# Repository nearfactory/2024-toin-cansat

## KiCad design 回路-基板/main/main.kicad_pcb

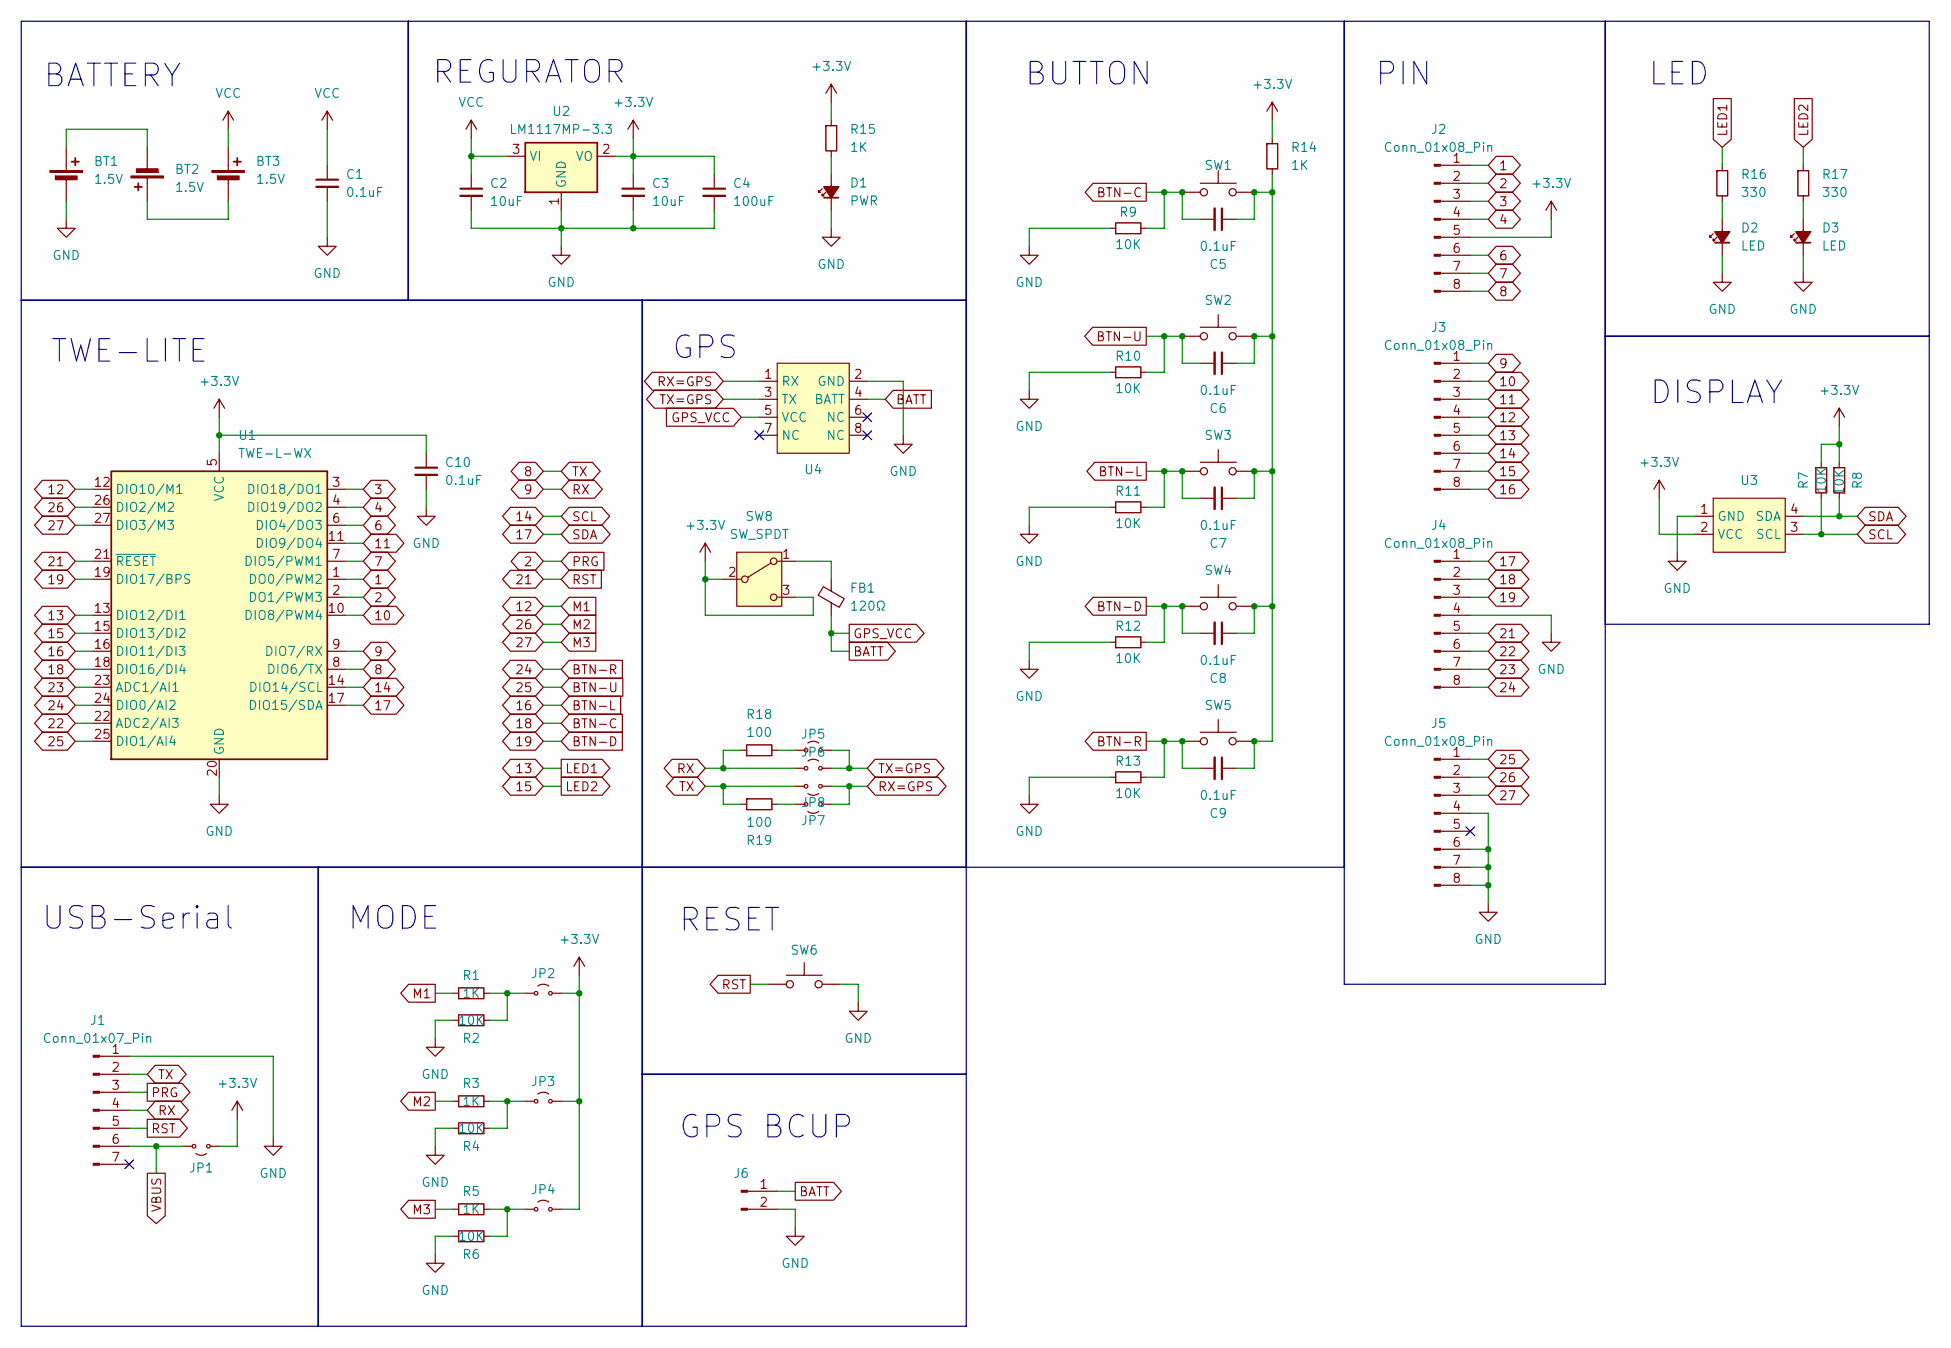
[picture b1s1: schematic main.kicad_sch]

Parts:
BT1, BT2, BT3: 1.5V; AAA-holder
C1, C5, C6, C7, C8, C9, C10: 0.1uF; C_0805_2012Metric
C2, C3: 10uF; C_0805_2012Metric
C4: 100uF; CP_Radial_D6.3mm_P2.50mm
D1: PWR; LED_0805_2012Metric
D2, D3: LED; LED_0805_2012Metric
FB1: 120Ω; L_0603_1608Metric
J1: Conn_01x07_Pin; PinSocket_1x07_P2.54mm_Vertical
J2, J3, J4, J5: Conn_01x08_Pin; Pin-Extender
J6: Conn_01x02_Pin; PinSocket_1x02_P2.54mm_Vertical
JP1, JP2, JP3, JP4, JP5, JP6, JP7, JP8: Jumper_2_Small_Open; SolderJumper-2_P1.3mm_Open_RoundedPad1.0x1.5mm
R1, R3, R5, R14, R15: 1K; R_0805_2012Metric
R2, R4, R6, R7, R8, R9, R10, R11, R12, R13: 10K; R_0805_2012Metric
R16, R17: 330; R_0805_2012Metric
R18, R19: 100; R_0805_2012Metric
SW1, SW2, SW3, SW4, SW5: SW_Push; TVBP06-B043C
SW6: SW_Push; Tactile1
SW8: SW_SPDT; SS12D01G4
U1: TWE-L-WX; MonoWireless_TWE-L-WX
U2: LM1117MP-3.3; SOT-223-3_TabPin2
U3: Display
U4: GPS-54D-014

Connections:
1: J2.1, U1.1 (DO0/PWM2)
2: J1.3, J2.2, U1.2 (DO1/PWM3)
3: J2.3, U1.3 (DIO18/DO1)
4: J2.4, U1.4 (DIO19/DO2)
6: J2.6, U1.6 (DIO4/DO3)
7: J2.7, U1.7 (DIO5/PWM1)
8: J1.2, J2.8, JP8.1 (A), R19.1, U1.8 (DIO6/TX)
9: J1.4, J3.1, JP6.1 (A), R18.1, U1.9 (DIO7/RX)
10: J3.2, U1.10 (DIO8/PWM4)
11: J3.3, U1.11 (DIO9/DO4)
12: J3.4, R1.1, U1.12 (DIO10/M1)
13: J3.5, R16.1, U1.13 (DIO12/DI1)
14: J3.6, R7.2, U1.14 (DIO14/SCL), U3.3 (SCL)
15: J3.7, R17.1, U1.15 (DIO13/DI2)
16: C7.2, J3.8, R11.2, SW3.1, U1.16 (DIO11/DI3)
17: J4.1, R8.2, U1.17 (DIO15/SDA), U3.4 (SDA)
18: C5.2, J4.2, R9.2, SW1.1, U1.18 (DIO16/DI4)
19: C8.2, J4.3, R12.2, SW4.1, U1.19 (DIO17/BPS)
21: J1.5, J4.5, SW6.1, U1.21 (~RESET); also elsewhere on the board
22: J4.6, U1.22 (ADC2/AI3)
23: J4.7, U1.23 (ADC1/AI1)
24: C9.2, J4.8, R13.2, SW5.1, U1.24 (DIO0/AI2)
25: C6.2, J5.1, R10.2, SW2.1, U1.25 (DIO1/AI4)
26: J5.2, R3.1, U1.26 (DIO2/M2)
27: J5.3, R5.1, U1.27 (DIO3/M3)
+3.3V: C3.1, C4.1, C10.1, J2.5, JP1.1 (A), JP2.2 (B), JP3.2 (B), JP4.2 (B), R7.1, R8.1, R14.1, R15.1, SW8.2 (B), SW8.3 (C), U1.5 (VCC), U2.2 (VO), U3.2 (VCC); also elsewhere on the board
BATT: FB1.2, J6.1, U4.4 (BATT), U4.5 (VCC)
GND: BT1.2 (-), C1.2, C2.2, C3.2, C4.2, C10.2, D1.1 (K), D2.1 (K), D3.1 (K), J1.1, J4.4, J5.4, J5.6, J5.7, J5.8, J6.2, R2.1, R4.1, R6.1, R9.1, R10.1, R11.1, R12.1, R13.1, SW6.2, U1.20 (GND), U1.28 (GND), U1.30 (GND), U1.31 (GND), U1.32 (GND), U2.1 (GND), U3.1 (GND), U4.2 (GND); also elsewhere on the board
unnamed: BT1.1 (+), BT2.2 (-)
unnamed: BT2.1 (+), BT3.2 (-)
unnamed: C5.1, C6.1, C7.1, C8.1, C9.1, R14.2, SW1.2, SW2.2, SW3.2, SW4.2, SW5.2
unnamed 31: D1.2 (A), R15.2; also elsewhere on the board
unnamed: D2.2 (A), R16.2
unnamed: D3.2 (A), R17.2
unnamed 34: JP2.1 (A), R1.2, R2.2; also elsewhere on the board
unnamed 35: JP3.1 (A), R3.2, R4.2; also elsewhere on the board
unnamed 36: JP4.1 (A), R5.2, R6.2; also elsewhere on the board
unnamed: JP5.1 (A), R18.2
unnamed: JP7.1 (A), R19.2
unnamed: FB1.1, SW8.1 (A)
RX=GPS: JP7.2 (B), JP8.2 (B), U4.1 (RX)
TX=GPS: JP5.2 (B), JP6.2 (B), U4.3 (TX)
VBUS: J1.6, JP1.2 (B); also elsewhere on the board
VCC: BT3.1 (+), C1.1, C2.1, U2.3 (VI)

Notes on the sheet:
GPS BCUP
DISPLAY
REGURATOR
RESET
TWE-LITE
USB-Serial
BUTTON
BATTERY
LED
GPS
MODE
PIN

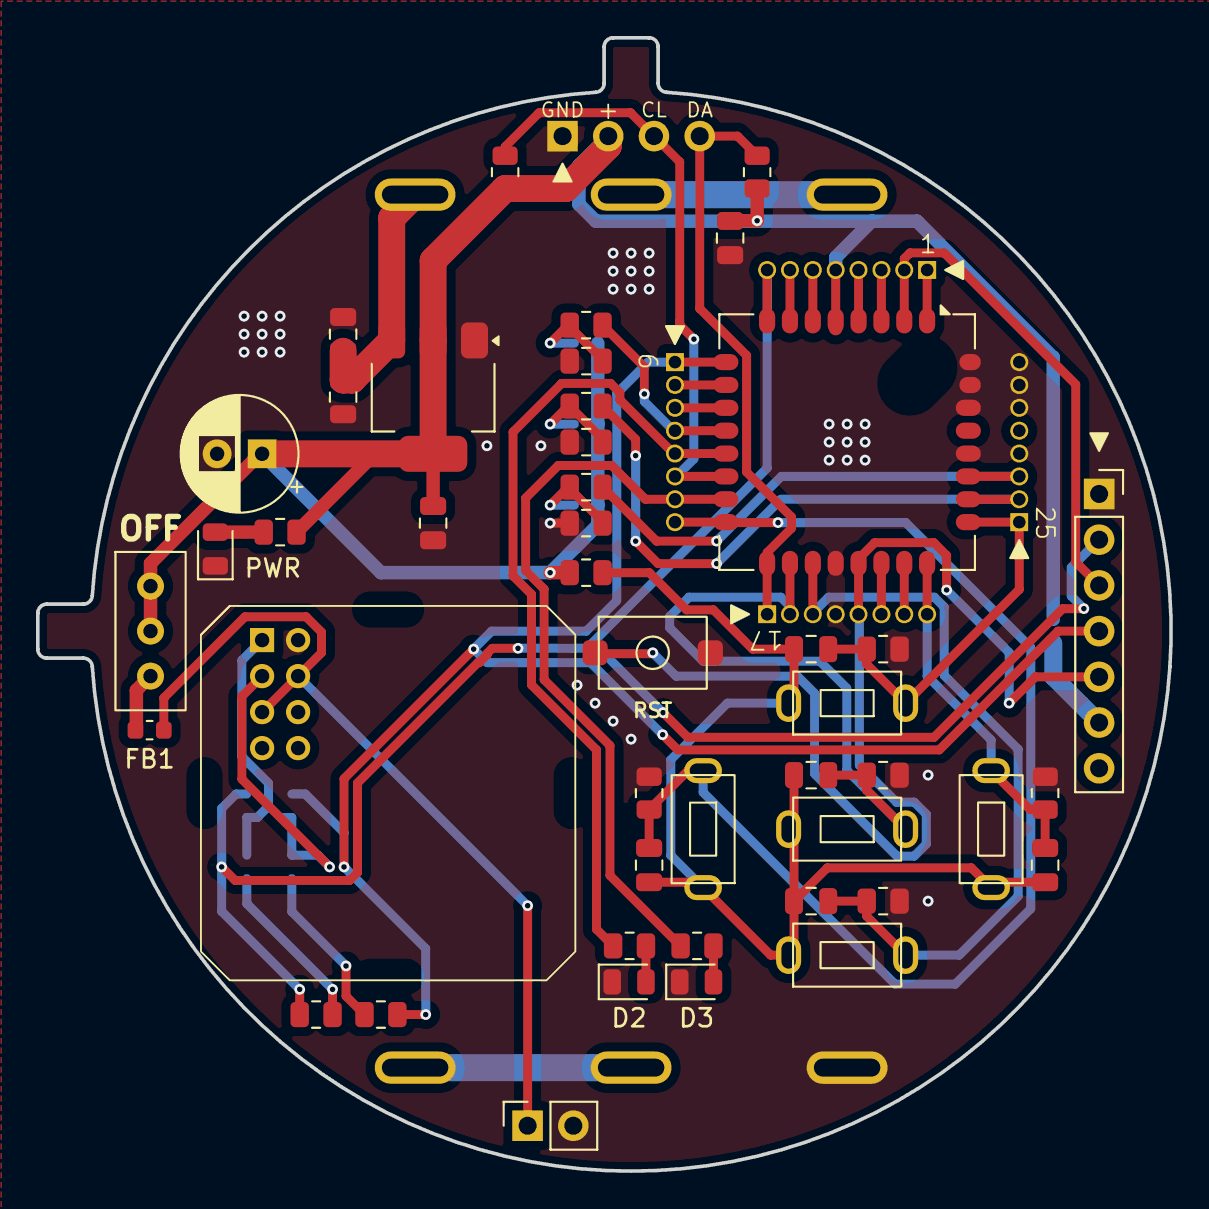
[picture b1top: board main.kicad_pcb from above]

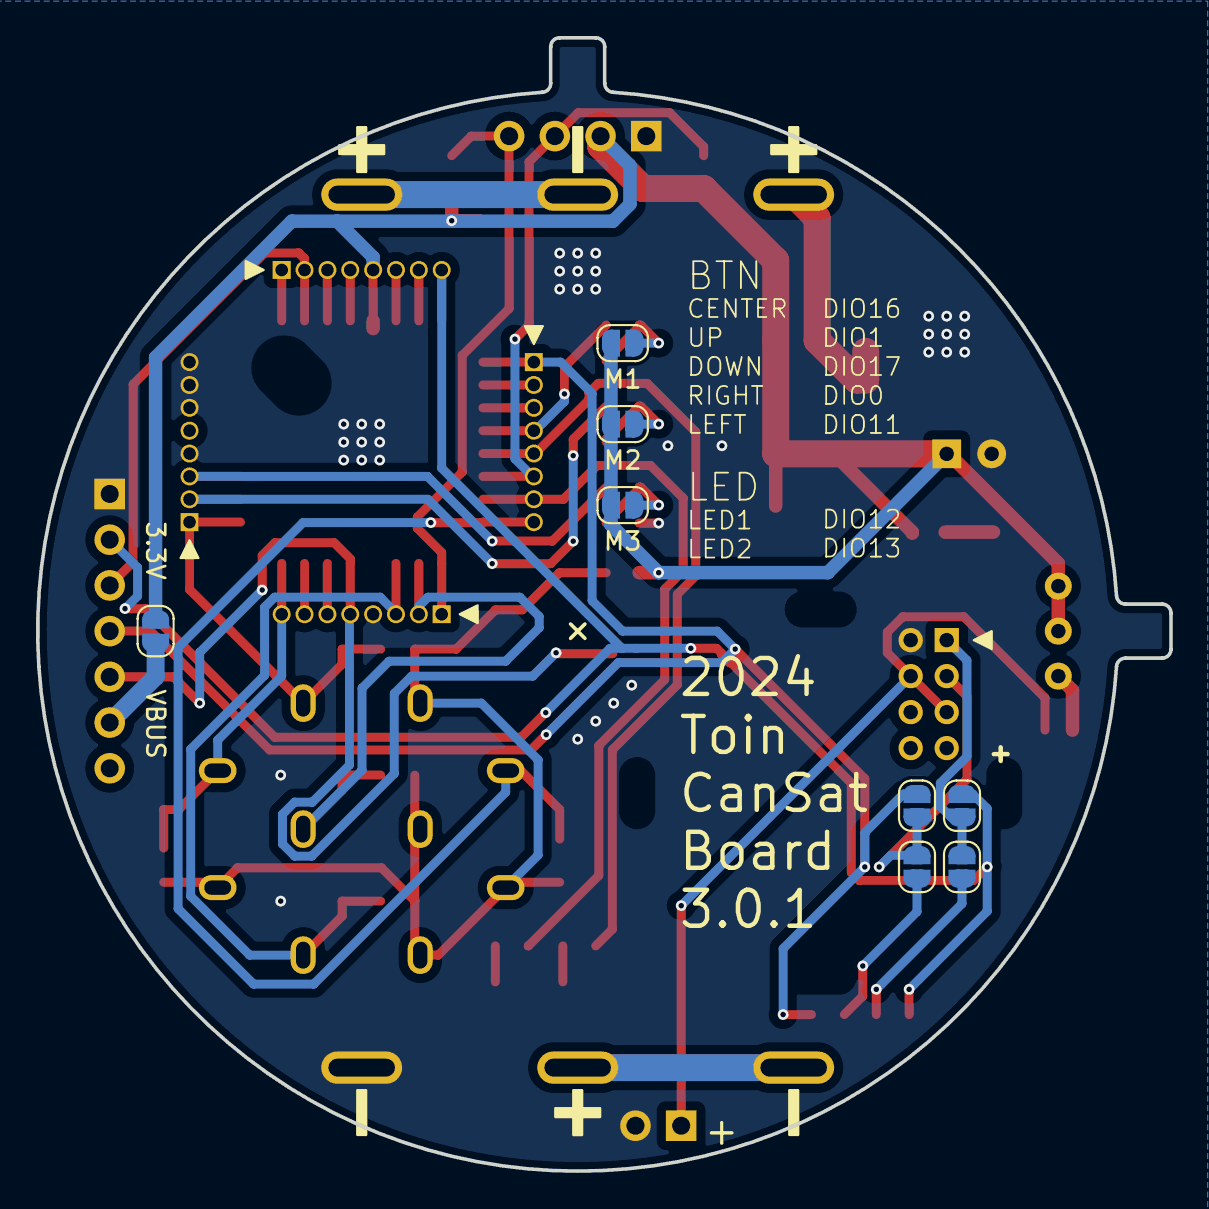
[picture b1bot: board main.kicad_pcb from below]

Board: 2 copper layers, 63.0 x 63.0 mm, 61 parts (11 on the bottom side), 44 nets.

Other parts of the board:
3.3V        VBUS: Jumper_2_Small_Open; SolderJumper-2_P1.3mm_Open_RoundedPad1.0x1.5mm
M1, M2, M3: Jumper_2_Small_Open; SolderJumper-2_P1.3mm_Open_RoundedPad1.0x1.5mm
PWR: PWR; LED_0805_2012Metric
RST: SW_Push; Tactile1

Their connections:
21: RST.1; also elsewhere on the board
+3.3V: 3.3V VBUS.1 (A), M1.2 (B), M2.2 (B), M3.2 (B); also elsewhere on the board
GND: PWR.1 (K), RST.2; also elsewhere on the board
unnamed 31: PWR.2 (A); also elsewhere on the board
unnamed 34: M1.1 (A); also elsewhere on the board
unnamed 35: M2.1 (A); also elsewhere on the board
unnamed 36: M3.1 (A); also elsewhere on the board
VBUS: 3.3V VBUS.2 (B); also elsewhere on the board

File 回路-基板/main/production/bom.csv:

Designator,Footprint,Quantity,Value,LCSC Part #
3.3V        VBUS,SolderJumper-2_P1.3mm_Open_RoundedPad1.0x1.5mm,1,Jumper_2_Small_Open,
"BT1, BT2, BT3",AAA-holder,3,1.5V,
"C1, C10, C5, C6, C7, C8, C9",0805,7,0.1uF,
"C2, C3",0805,2,10uF,
C4,CP_Radial_D6.3mm_P2.50mm,1,100uF,
"D2, D3",0805,2,LED,
FB1,0603,1,FerriteBead_Small,
J1,PinSocket_1x07_P2.54mm_Vertical,1,Conn_01x07_Pin,
"J2, J3, J4, J5",Pin-Extender,4,Conn_01x08_Pin,
"PRG, RST",Tactile1,2,SW_Push,
PWR,0805,1,PWR,
"R1, R14, R15, R3, R5",0805,5,1K,
"R10, R11, R12, R13, R2, R4, R6, R7, R8, R9",0805,10,10K,
"R16, R17",0805,2,330,
"SW1, SW2, SW3, SW4, SW5",TVBP06-B043C,5,SW_Push,
SW8,SS12D01G4,1,SW_SPDT,
U1,MonoWireless_TWE-L-WX,1,TWE-L-WX,
U2,SOT-223-3_TabPin2,1,LM1117MP-3.3,
U3,Display,1,~,
U4,GPS-54D-014,1,~,

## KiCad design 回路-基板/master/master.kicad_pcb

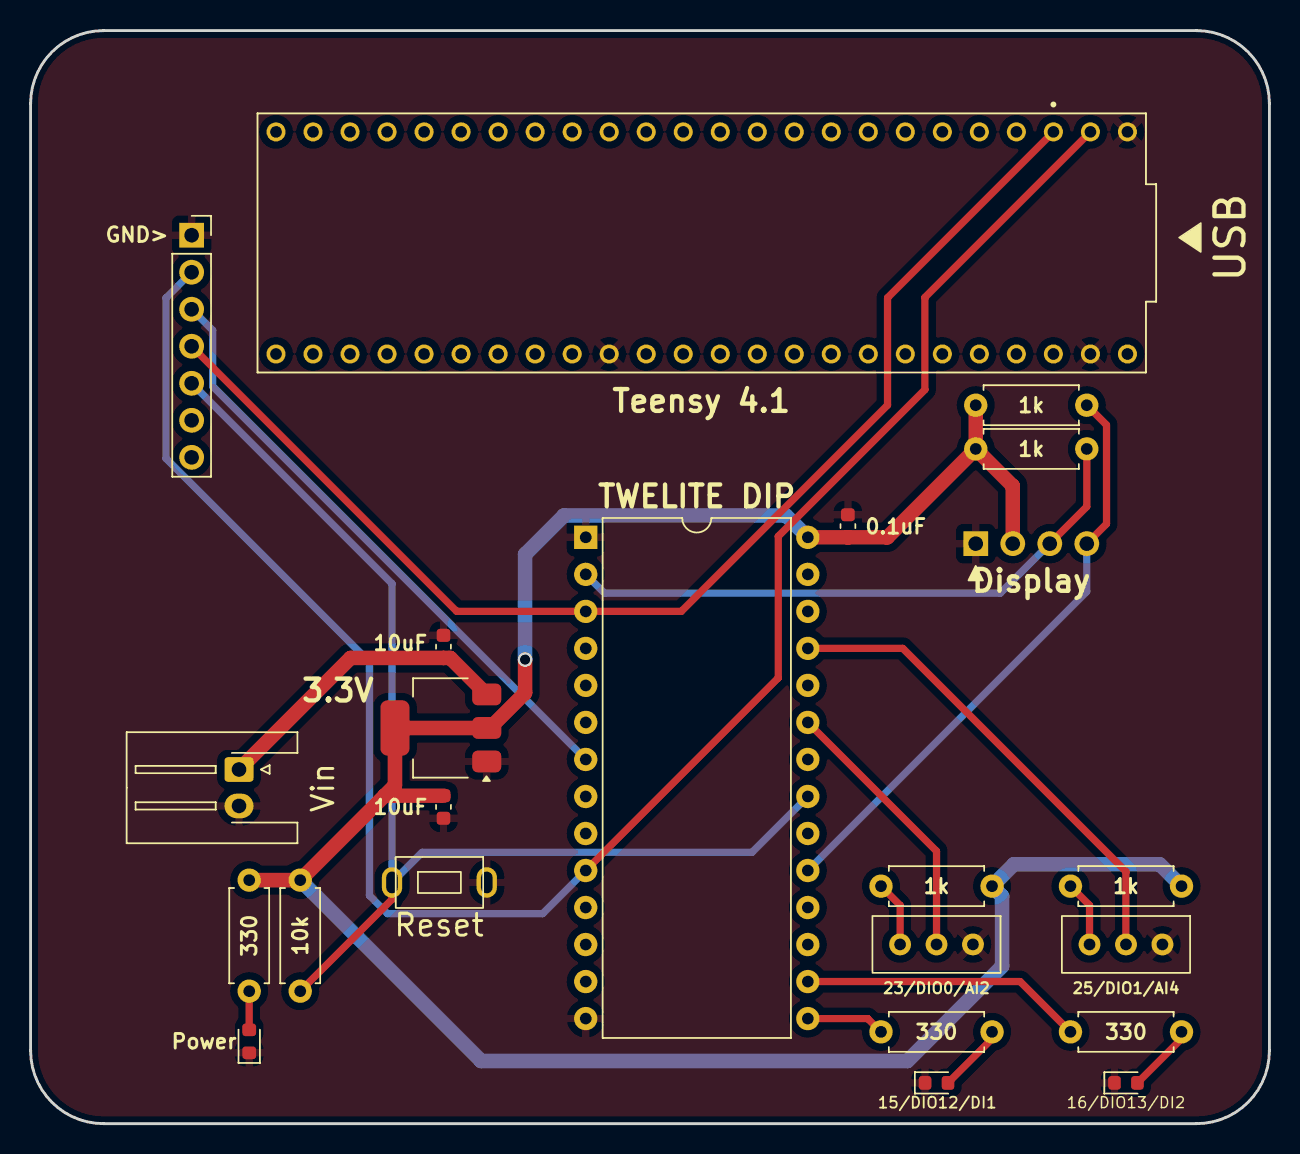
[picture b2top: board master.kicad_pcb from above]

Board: 2 copper layers, 85.0 x 75.0 mm, 23 parts (0 on the bottom side), 18 nets.

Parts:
3.3V: LM1117MP-3.3; SOT-223-3_TabPin2
15/DIO12/DI1: LED1; LED_0603_1608Metric
16/DIO13/DI2: LED2; LED_0603_1608Metric
23/DIO0/AI2, 25/DIO1/AI4: SW_SPDT; SS12D01G4
C1, C3: 10uF; C_0603_1608Metric
C2: 0.1uF; C_0603_1608Metric
Display: Display
GND>: Conn_01x07_Pin; PinSocket_1x07_P2.54mm_Vertical
Power: PWR; LED_0603_1608Metric
R1, R2, R3: 330; R_Axial_DIN0207_L6.3mm_D2.5mm_P7.62mm_Horizontal
R4, R5: 1K; R_Axial_DIN0207_L6.3mm_D2.5mm_P7.62mm_Horizontal
R6: 10K; R_Axial_DIN0207_L6.3mm_D2.5mm_P7.62mm_Horizontal
R7, R8: R_Small; R_Axial_DIN0207_L6.3mm_D2.5mm_P7.62mm_Horizontal
Reset: RESET; TVBP06-B043C
TWELITE DIP: TWE-L-DP-W; DIP-28_W15.24mm
Teensy 4.1: DEV-16771; MODULE_DEV-16771
Vin: Ext. PWR; JST_XH_S2B-XH-A-1_1x02_P2.50mm_Horizontal

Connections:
2: Display.3 (SCL), R4.1, TWELITE DIP.2 (DIO14/SCL)
3: GND>.4, TWELITE DIP.3 (DIO7/RX), Teensy 4.1.1 (TX1)
7: GND>.3, TWELITE DIP.7 (DO1/PWM3)
10: GND>.2, TWELITE DIP.10 (DIO6/TX), Teensy 4.1.0 (RX1)
15: R2.1, TWELITE DIP.15 (DIO12/DI1)
16: R3.1, TWELITE DIP.16 (DIO13/DI2)
19: Display.4 (SDA), R5.1, TWELITE DIP.19 (DIO15/SDA)
21: GND>.5, R6.2, Reset.1, TWELITE DIP.21 (~RESET)
23: 23/DIO0/AI2.2 (B), TWELITE DIP.23 (DIO0/AI2)
25: 25/DIO1/AI4.2 (B), TWELITE DIP.25 (DIO1/AI4)
+3.3V: 3.3V.2 (VO), C2.1, C3.1, Display.2 (VCC), R1.1, R4.2, R5.2, R6.1, R7.2, R8.2, TWELITE DIP.28 (VCC)
GND: 3.3V.1 (GND), 15/DIO12/DI1.1 (K), 16/DIO13/DI2.1 (K), 23/DIO0/AI2.3 (C), 25/DIO1/AI4.3 (C), C1.2, C2.2, C3.2, Display.1 (GND), GND>.1, Power.1 (K), Reset.2, TWELITE DIP.1 (GND), TWELITE DIP.14 (GND), Teensy 4.1.GND1 (GND), Teensy 4.1.GND2 (GND), Teensy 4.1.GND3 (GND), Vin.2
unnamed: Power.2 (A), R1.2
unnamed: 15/DIO12/DI1.2 (A), R2.2
unnamed: 16/DIO13/DI2.2 (A), R3.2
unnamed: 3.3V.3 (VI), C1.1, Vin.1
unnamed: 23/DIO0/AI2.1 (A), R7.1
unnamed: 25/DIO1/AI4.1 (A), R8.1

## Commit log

2024-04-11 TWE-LITEデータシートの追加
2024-04-11 回路関連のプッシュ
2024-04-11 TWE-LITE-RED_symbol
2024-04-11 過去作の追加
2024-04-16 3Dモデルをアップロード
    よろちく～～～～～
2024-04-16 3Dモデルの名前変更した
2024-04-17 回路をアップデートした
2024-04-19 回路やったぜぇ
2024-04-19 回路更新
2024-04-20 右下のトランジスタの種類変えたよ
2024-04-20 バージョン4（仮配置）の追加
2024-04-20 回路の電源部分をバッテリーに変更した
    コネクタからバッテリーx2に変更したよ
2024-05-01 GPSとTWELITEの3Dモデル作った、KiCadで基板上に配置する時にでも使ってください
2024-05-06 PCB半分完成
2024-05-09 回路やり直したよ
    山本さんからのアドバイス部分を修正
2024-05-19 回路関連
2024-05-19 jpegにしたよ
2024-05-31 回路のPDFを追加したよ
2024-05-31 マスター側のTeensyのプログラムを追加したよ
    左右ボタンでアルファベットを選べるよ
2024-06-01 ディスプレイの日本語表示サンプルを追加したよ
2024-06-01 文字入力用のプログラムを追加したよ
    文字入力が可能になった
2024-06-01 回路とPCBを更新したものを追加
2024-06-02 デスクトップアプリのプログラムを追加した
2024-06-03 子機基板の回路図を更新した
2024-06-03 事後プレゼンスライド追加
2024-06-03 回路図を修正、PCBを作成し始めた（直径60）
    電池の配置場所がわからん...
2024-06-03 回路図の裏表の画像を出力し追加した
2024-06-04 PCBデザインを更新
    単4電池3本分のサイズをとってみた、きつい
2024-06-08 回路図/PCB両方一応完成した
2024-06-09 メインのPCBを更新した
2024-06-09 JLCPCB用の出力ファイルなどを追加
2024-06-09 電源用のLEDのつけ忘れを慌てて修正したよ
2024-06-09 ちょっと見たらファイル書き換えられてたから一応
2024-06-10 設計用データを追加した
2024-06-15 プレゼン関連の資料を追加
2024-06-27 事前資料を追加
2024-06-29 回路図とPCBを修正した
2024-06-30 回路図とPCBを修正してJLCPCB用のファイルを出力した
2024-06-30 回路図とPCBを更新
    GPSの電源のオンオフ式に切り替え
2024-06-30 Create webSerial
    web上でシリアルの状態を確認できるやつ
2024-06-30 ばーじょん4（カバー込み）アップ
2024-06-30 基板外形を更新したPCBを製造用ファイルに出力した
2024-07-01 拡張子つけたよん
2024-07-03 基板関連色々やった
2024-07-11 プログラム追加した
2024-07-12 ディスプレイのテストプログラムを追加した
    ディスプレイの表示に成功した
2024-07-13 ピンのテストプログラムと基板の更新版PCB
    PCBのDRよろしくー
2024-07-13 回路 v3 完成したよ
2024-07-13 スライドスイッチの3Dモデルを追加
2024-07-13 ヴぁーじょん5（カバー込み）作ったよ！！！！！！！！！！！4時間で終わらせた俺をほめてくれ
2024-07-13 基板関連のファイルです
2024-07-13 プログラムのファイルとかを追加
2024-07-13 TWELITE ProgrammerとTWELITE STAGEを追加した
2024-07-14 事前プレゼン資料完成 ～それに使用した素材まとめpptxとともに～
2024-07-14 プログラム@寺田を追加①
2024-07-14 ぷろぐらむ＠てらだをついか②
2024-07-14 プログラム＠テラダヲツイカ③
2024-07-14 プレゼン資料を追加
2024-07-15 事後プレゼン更新&基板回路図/PCBデザイン更新
    DRとかいろいろちぇっくよろしくー
2024-07-16 いろいろ追加したよ
2024-07-16 今日の進捗を一覧化したよ
2024-07-16 基板とかのファイルをいじったよ
2024-07-16 親機基板を作成した
    回路図のDRよろしく
2024-07-17 親機基板のPCBを少し進めた
2024-07-17 今日の進捗
2024-07-17 うぇぶシリアル0717ヴぁーじょん
2024-07-17 模擬GPSデータ かっこよくした
2024-07-17 ファイル変更
2024-07-17 マップ表示
2024-07-18 今日の進捗、結構形できたから親機完成するまでいったんステイ
2024-08-10 回路図の電源周りを整備した+フットプリントリンクさせた
    RX/TXは多分大丈夫だと思う、DRお願い
2024-08-10 開けないのを改善したいなぁ
2024-08-10 再度フットプリント関連付けした
2024-08-10 PCB_1
2024-08-10 PCB進めた
    発注用ファイルも作成した
2024-08-14 子機基板のまずいところを修正して発注用ファイルを出力
    一部PCBA部品が裏になってたのを表に修正した
2024-08-16 事前プレゼン映像用のPFを追加した
2024-08-17 台本と3Dモデルを追加した
2024-08-17 台本を編集した
2024-08-18 音声と3Dを追加した
2024-08-18 音声入れた
2024-08-19 字幕を追加した
2024-08-19 font
2024-08-19 フォント追加
2024-08-19 編集した
    ミッション・サクセスクライテリアあたり
2024-08-19 編集した
2024-08-20 音声追加
2024-08-20 字幕追加
2024-08-20 編集
    03 03.5 05 07 11 20 21 22 23 24
2024-08-21 01 02 08 25
2024-08-22 3dやった
2024-08-22 色々編集した
    あとちょっと...
2024-08-23 一旦編集終わった
2024-08-29 ファイル整理した
2024-09-05 事後プレゼン用の子機レンダリング画像を追加した
2024-09-05 事後プレゼン更新
2024-09-06 プレゼン更新。
2024-09-06 子機のシルエットを追加した
2024-09-06 白と元の人の色のシルエットを追加した
2024-09-06 Whiteを白にした
2024-09-07 プレゼン更新 & プログラムバックアップ
2024-09-07 子機の画像を追加
2024-09-07 子機画像更新
2024-09-09 プレゼンのPDFバージョンを追加
2024-09-09 zip化して追加
2024-09-09 映像関係
2025-02-03 マップの情報のやつを追加した
